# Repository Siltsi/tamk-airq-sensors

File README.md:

# TAMK AIRQ SENSORS  

## TEAM25  

**Members**  
- Eino Lausmaa ([@eino](https://github.com/LausmaaEino))  
- Samu Ojala ([@samu](https://github.com/SamuOj))  
- Tomi Tienhaara ([@tomi](https://github.com/TomiTien))  
- Totti Sillanpää ([@totti](https://github.com/Siltsi))  

## About  

This repository contains a hardware project developed for the **TAMK Summer Training 2025**. The project goal is to design and manifacture a custom circuit board and enclosure for **PCB-based particle sensor systems**.  

All PCBs in this project were designed using **KiCad**.  

## Models  

### ttgo_airq  

The **ttgo_airq** model is based on the LILYGO [T-Display](https://lilygo.cc/products/t-display). This model is currently in a **usable and tested state**.  

**Features:**  
- ESP32 with integrated display  
- Custom-designed PCB  
- 2 enclosure options  

**Enclosures:**  
- **Medium enclosure**  
  - Supports Sensirion [SEN5x](https://sensirion.com/products/catalog/SEK-SEN5x)  
  - Supports Sensirion [SCD41](https://sensirion.com/products/catalog/SEK-SCD41)  
- **Small enclosure**  
  - Supports Sensirion [SCD41](https://sensirion.com/products/catalog/SEK-SCD41) only  

### nodemcu_airq  

The **nodemcu_airq** model is based on the Joy-IT [NodeMCU ESP32](https://joy-it.net/en/products/SBC-NodeMCU-ESP32).  
This model is **still a work in progress**.  

**Current status:**  
- PCB design is expected to be functional  
- System-level development is ongoing  

**Display options:**  
- Large display using the Velleman [VMP400](https://www.velleman.eu/products/view/3-5-320-x-480-touchscreen-for-raspberry-pi-vmp400/?id=438240)  
- Smaller display  
- No display  

**Enclosures:**  
- No enclosures have been designed yet for this model

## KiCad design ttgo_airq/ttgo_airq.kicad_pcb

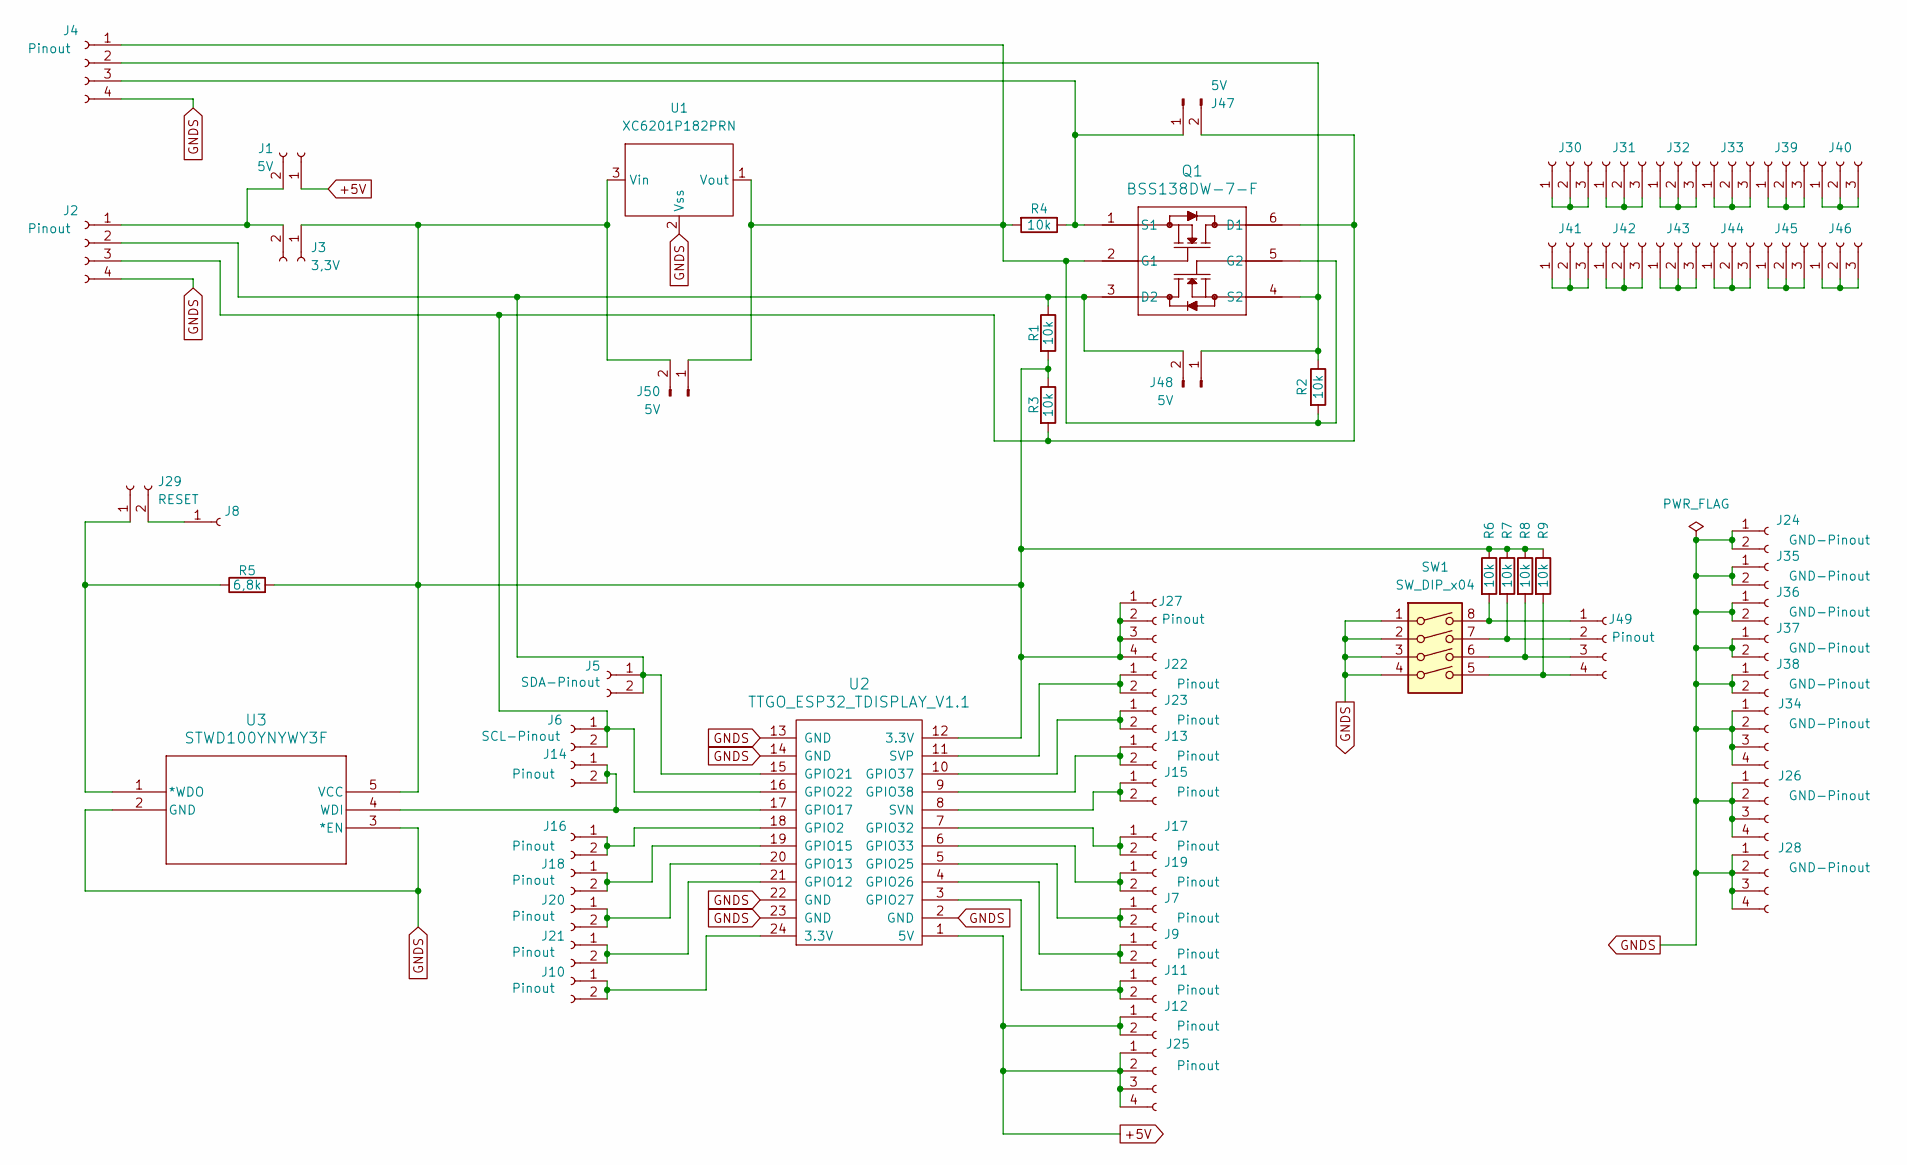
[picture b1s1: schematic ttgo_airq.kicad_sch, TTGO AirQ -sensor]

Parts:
J1: 5V; PinSocket_1x02_P2.54mm_Vertical
J2, J4, J25, J27, J49: Pinout; PinSocket_1x04_P2.54mm_Vertical
J3: 3,3V; PinSocket_1x02_P2.54mm_Vertical
J5: SDA-Pinout; PinSocket_1x02_P2.54mm_Vertical
J6: SCL-Pinout; PinSocket_1x02_P2.54mm_Vertical
J7, J9, J10, J11, J12, J13, J14, J15, J16, J17, J18, J19, J20, J21, J22, J23: Pinout; PinSocket_1x02_P2.54mm_Vertical
J8: PinSocket_1x01_P2.54mm_Vertical
J24, J35, J36, J37, J38: GND-Pinout; PinSocket_1x02_P2.54mm_Vertical
J26, J28, J34: GND-Pinout; PinSocket_1x04_P2.54mm_Vertical
J29: RESET; PinSocket_1x02_P2.54mm_Vertical
J30, J31, J32, J33, J39, J40, J41, J42, J43, J44, J45, J46: Conn_01x03_Socket; PinSocket_1x03_P2.54mm_Vertical
J47, J48, J50: 5V; PinHeader_1x02_P2.54mm_Vertical
Q1: BSS138DW-7-F; SOT363_DIO
R1, R2, R3, R4, R6, R7, R8, R9: 10k; R_1206_3216Metric_Pad1.30x1.75mm_HandSolder
R5: 6,8k; R_1206_3216Metric_Pad1.30x1.75mm_HandSolder
SW1: SW_DIP_x04; SW_DIP_SPSTx04_Piano_10.8x11.72mm_W7.62mm_P2.54mm
U1: XC6201P182PRN
U2: TTGO_ESP32_TDISPLAY_V1.1; TTGO-T-Display
U3: STWD100YNYWY3F; SOT23-5L_STM

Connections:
+5V: J1.1, J12.1, J12.2, J25.1, J25.2, J25.3, J25.4, U2.1 (5V)
GNDS: J2.4, J4.4, J24.1, J24.2, J26.1, J26.2, J26.3, J26.4, J28.1, J28.2, J28.3, J28.4, J34.1, J34.2, J34.3, J34.4, J35.1, J35.2, J36.1, J36.2, J37.1, J37.2, J38.1, J38.2, SW1.1, SW1.2, SW1.3, SW1.4, U1.2 (Vss), U2.2 (GND), U2.13 (GND), U2.14 (GND), U2.22 (GND), U2.23 (GND), U3.2 (GND), U3.3 (*EN)
unnamed: J1.2, J2.1, J3.2
unnamed: J2.2, J5.1, J5.2, J48.2, Q1.3 (D2), R1.1, U2.15 (GPIO21)
unnamed: J2.3, J6.1, J6.2, J47.2, Q1.6 (D1), R3.2, U2.16 (GPIO22)
unnamed: J4.1, J50.1, Q1.2 (G1), Q1.5 (G2), R2.2, R4.2, U1.1 (Vout)
unnamed: J4.2, J48.1, Q1.4 (S2), R2.1
unnamed: J4.3, J47.1, Q1.1 (S1), R4.1
unnamed: J7.1, J7.2, U2.5 (GPIO25)
unnamed: J9.1, J9.2, U2.4 (GPIO26)
unnamed: J10.1, J10.2, U2.24 (3.3V)
unnamed: J11.1, J11.2, U2.3 (GPIO27)
unnamed: J13.1, J13.2, U2.9 (GPIO38)
unnamed: J14.1, J14.2, U2.17 (GPIO17), U3.4 (WDI)
unnamed: J15.1, J15.2, U2.8 (SVN)
unnamed: J16.1, J16.2, U2.18 (GPIO2)
unnamed: J17.1, J17.2, U2.7 (GPIO32)
unnamed: J18.1, J18.2, U2.19 (GPIO15)
unnamed: J19.1, J19.2, U2.6 (GPIO33)
unnamed: J20.1, J20.2, U2.20 (GPIO13)
unnamed: J21.1, J21.2, U2.21 (GPIO12)
unnamed: J22.1, J22.2, U2.11 (SVP)
unnamed: J23.1, J23.2, U2.10 (GPIO37)
unnamed: J3.1, J27.1, J27.2, J27.3, J27.4, J50.2, R1.2, R3.1, R5.2, R6.1, R7.1, R8.1, R9.1, U1.3 (Vin), U2.12 (3.3V), U3.5 (VCC)
unnamed: J29.1, R5.1, U3.1 (*WDO)
unnamed: J8.1, J29.2
unnamed: J30.1, J30.2, J30.3
unnamed: J31.1, J31.2, J31.3
unnamed: J32.1, J32.2, J32.3
unnamed: J33.1, J33.2, J33.3
unnamed: J39.1, J39.2, J39.3
unnamed: J40.1, J40.2, J40.3
unnamed: J41.1, J41.2, J41.3
unnamed: J42.1, J42.2, J42.3
unnamed: J43.1, J43.2, J43.3
unnamed: J44.1, J44.2, J44.3
unnamed: J45.1, J45.2, J45.3
unnamed: J46.1, J46.2, J46.3
unnamed: J49.1, R6.2, SW1.8
unnamed: J49.2, R7.2, SW1.7
unnamed: J49.3, R8.2, SW1.6
unnamed: J49.4, R9.2, SW1.5

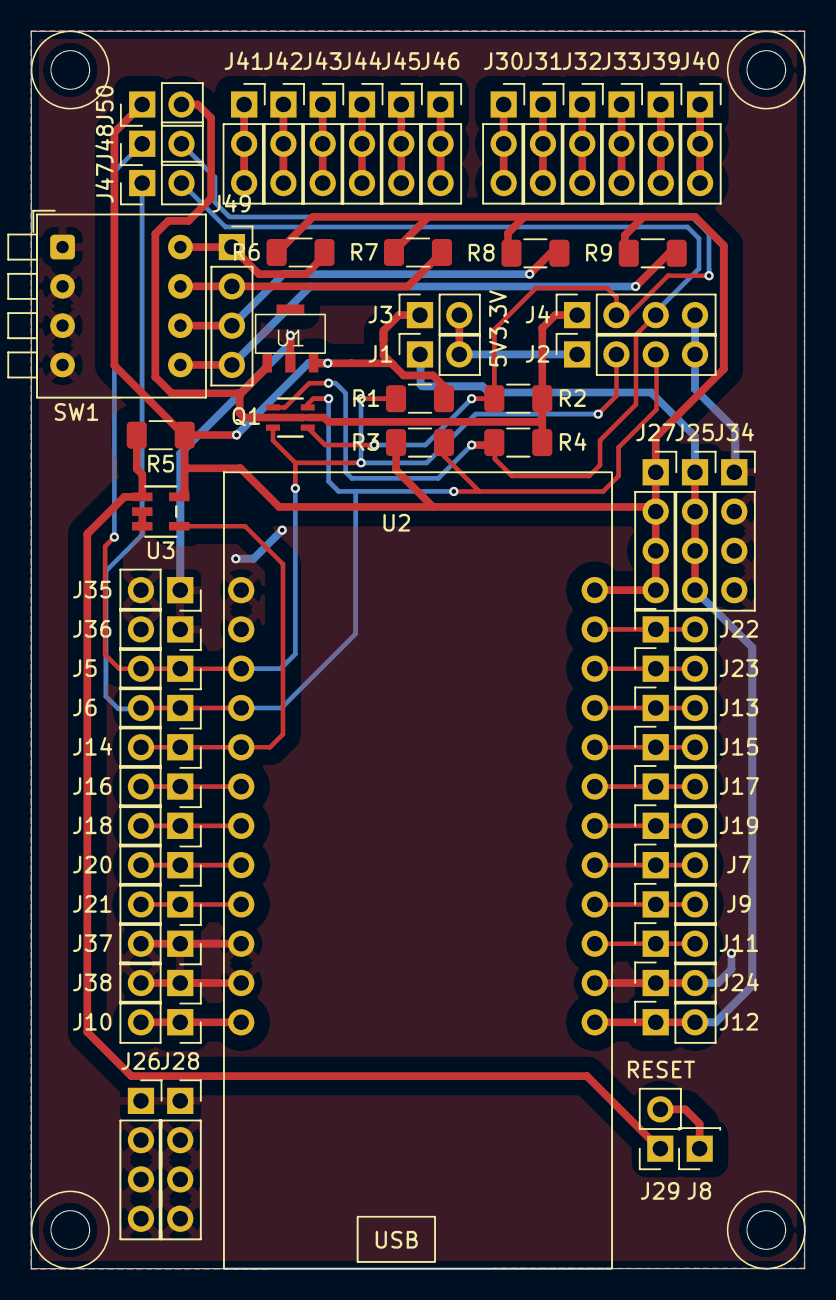
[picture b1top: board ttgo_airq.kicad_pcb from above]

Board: 2 copper layers, 50.0 x 80.0 mm, 64 parts (0 on the bottom side), 42 nets.

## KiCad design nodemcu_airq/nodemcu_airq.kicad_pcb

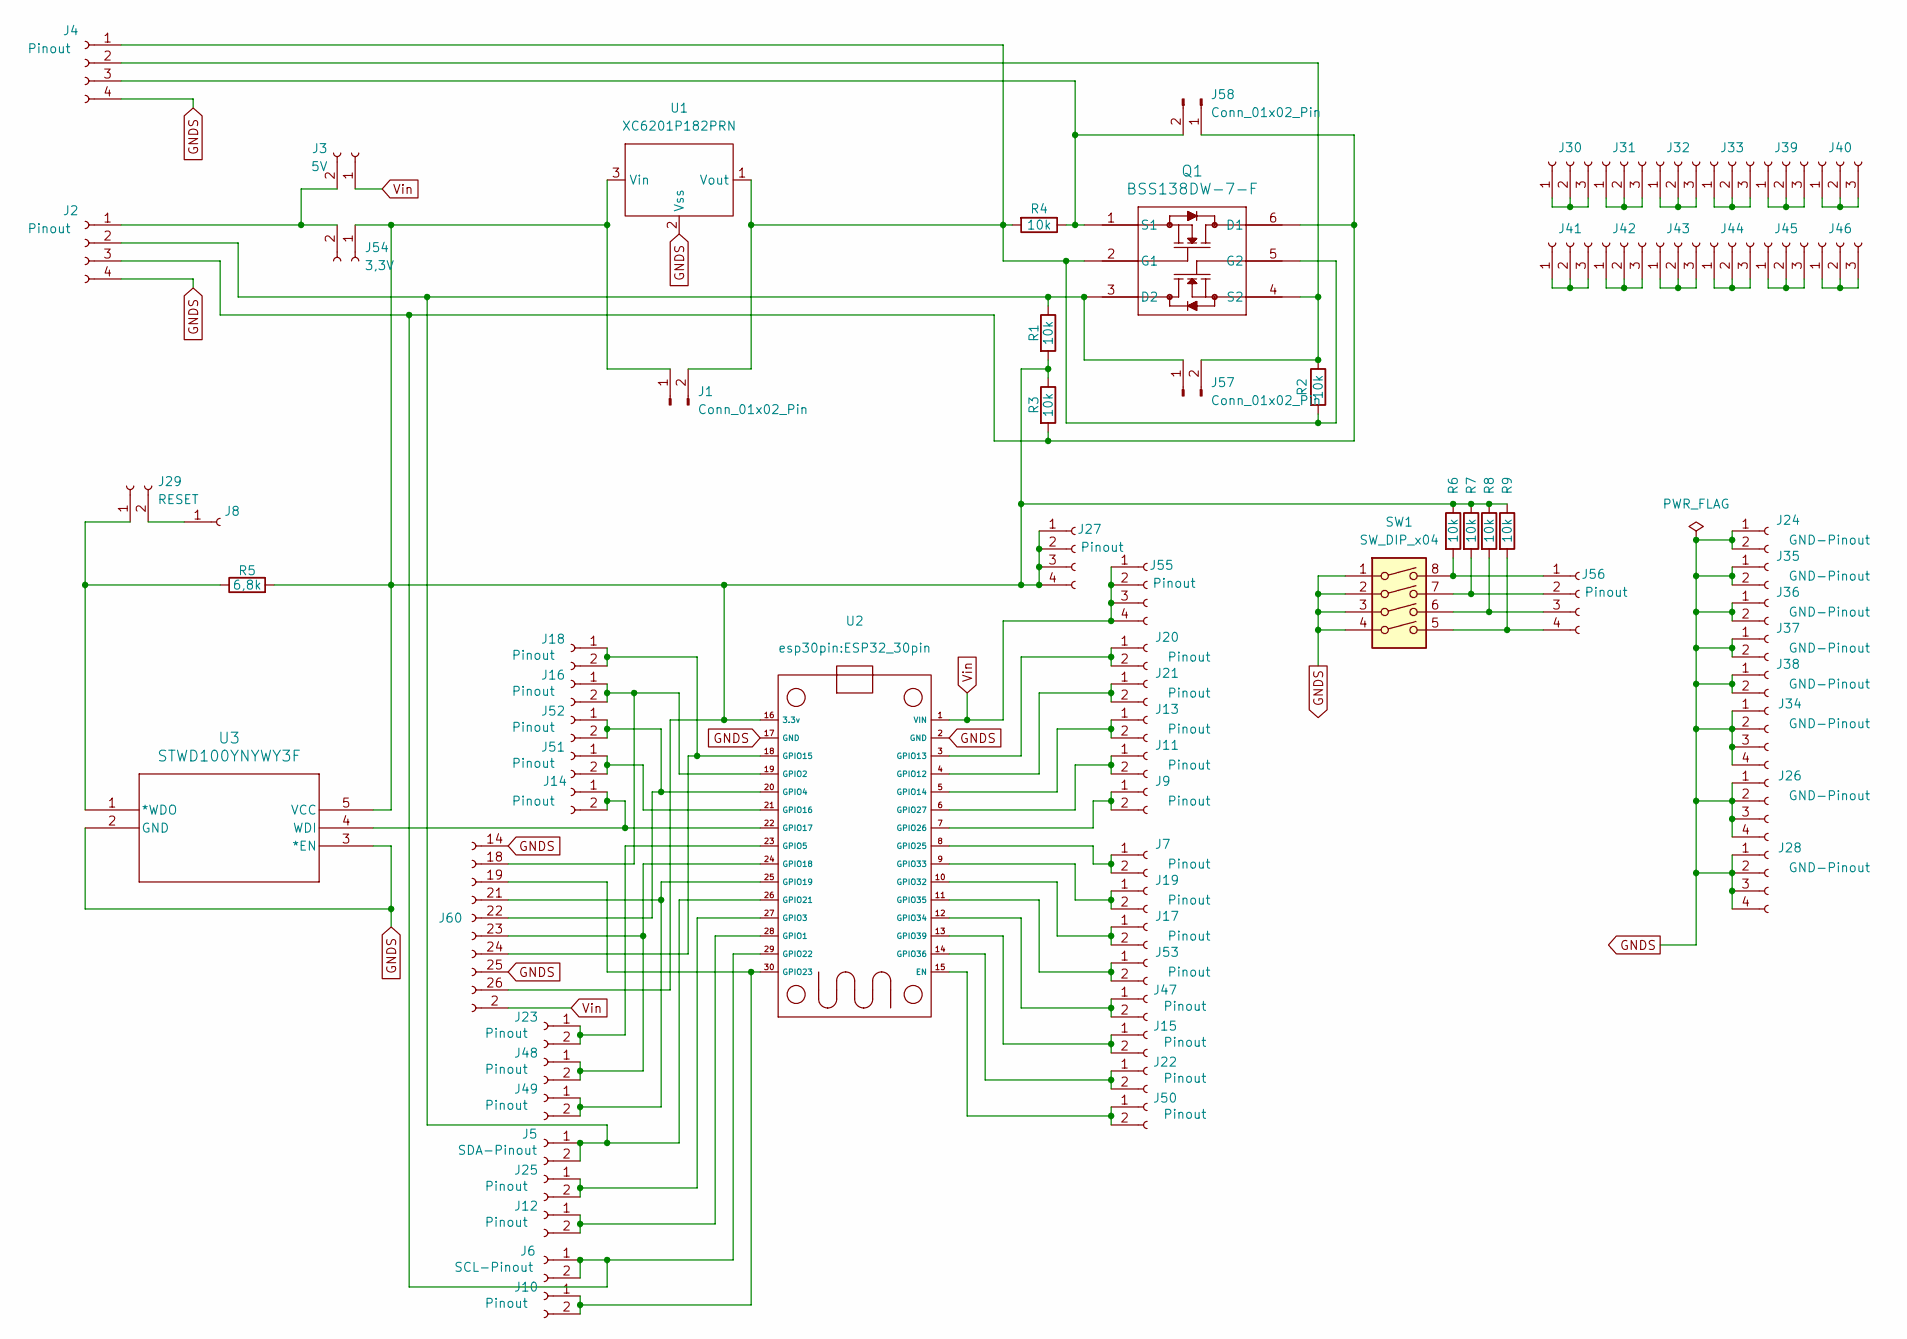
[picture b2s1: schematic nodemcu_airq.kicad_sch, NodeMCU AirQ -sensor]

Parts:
J1, J57, J58: Conn_01x02_Pin; PinHeader_1x02_P2.54mm_Vertical
J2, J4, J27, J55, J56: Pinout; PinSocket_1x04_P2.54mm_Vertical
J3: 5V; PinSocket_1x02_P2.54mm_Vertical
J5: SDA-Pinout; PinSocket_1x02_P2.54mm_Vertical
J6: SCL-Pinout; PinSocket_1x02_P2.54mm_Vertical
J7, J9, J10, J11, J12, J13, J14, J15, J16, J17, J18, J19, J20, J21, J22, J23, J25, J47, J48, J49, J50, J51, J52, J53: Pinout; PinSocket_1x02_P2.54mm_Vertical
J8: PinSocket_1x01_P2.54mm_Vertical
J24, J35, J36, J37, J38: GND-Pinout; PinSocket_1x02_P2.54mm_Vertical
J26, J28, J34: GND-Pinout; PinSocket_1x04_P2.54mm_Vertical
J29: RESET; PinSocket_1x02_P2.54mm_Vertical
J30, J31, J32, J33, J39, J40, J41, J42, J43, J44, J45, J46: Conn_01x03_Socket; PinSocket_1x03_P2.54mm_Vertical
J54: 3,3V; PinSocket_1x02_P2.54mm_Vertical
J60: Conn_01x10_Socket; PinSocket_2x13_P2.54mm_Vertical
Q1: BSS138DW-7-F; SOT363_DIO
R1, R2, R3, R4, R6, R7, R8, R9: 10k; R_1206_3216Metric_Pad1.30x1.75mm_HandSolder
R5: 6,8k; R_1206_3216Metric_Pad1.30x1.75mm_HandSolder
SW1: SW_DIP_x04; SW_DIP_SPSTx04_Piano_10.8x11.72mm_W7.62mm_P2.54mm
U1: XC6201P182PRN
U2: ESP32_30pin
U3: STWD100YNYWY3F; SOT23-5L_STM

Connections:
GNDS: J2.4, J4.4, J24.1, J24.2, J26.1, J26.2, J26.3, J26.4, J28.1, J28.2, J28.3, J28.4, J34.1, J34.2, J34.3, J34.4, J35.1, J35.2, J36.1, J36.2, J37.1, J37.2, J38.1, J38.2, J60.14 (Pin_1), J60.25 (Pin_8), SW1.1, SW1.2, SW1.3, SW1.4, U1.2 (Vss), U2.2 (GND), U2.17 (GND), U3.2 (GND), U3.3 (*EN)
unnamed: J1.1, J27.1, J27.2, J27.3, J27.4, J54.1, J60.26 (Pin_9), R1.2, R3.1, R5.2, R6.1, R7.1, R8.1, R9.1, U1.3 (Vin), U2.16 (3.3v), U3.5 (VCC)
unnamed: J1.2, J4.1, Q1.2 (G1), Q1.5 (G2), R2.2, R4.2, U1.1 (Vout)
unnamed: J2.1, J3.2, J54.2
unnamed: J2.2, J5.1, J5.2, J57.1, Q1.3 (D2), R1.1, U2.26 (GPIO21)
unnamed: J2.3, J6.1, J6.2, J58.1, Q1.6 (D1), R3.2, U2.29 (GPIO22)
unnamed: J4.2, J57.2, Q1.4 (S2), R2.1
unnamed: J4.3, J58.2, Q1.1 (S1), R4.1
unnamed: J7.1, J7.2, U2.8 (GPIO25)
unnamed: J9.1, J9.2, U2.7 (GPIO26)
unnamed: J10.1, J10.2, J60.19 (Pin_3), U2.30 (GPIO23)
unnamed: J11.1, J11.2, U2.6 (GPIO27)
unnamed: J12.1, J12.2, U2.28 (GPIO1)
unnamed: J13.1, J13.2, U2.5 (GPIO14)
unnamed: J14.1, J14.2, U2.22 (GPIO17), U3.4 (WDI)
unnamed: J15.1, J15.2, U2.13 (GPIO39)
unnamed: J16.1, J16.2, J60.18 (Pin_2), U2.19 (GPIO2)
unnamed: J17.1, J17.2, U2.10 (GPIO32)
unnamed: J18.1, J18.2, J60.24 (Pin_7), U2.18 (GPIO15)
unnamed: J19.1, J19.2, U2.9 (GPIO33)
unnamed: J20.1, J20.2, U2.3 (GPIO13)
unnamed: J21.1, J21.2, U2.4 (GPIO12)
unnamed: J22.1, J22.2, U2.14 (GPIO36)
unnamed: J23.1, J23.2, U2.23 (GPIO5)
unnamed: J25.1, J25.2, U2.27 (GPIO3)
unnamed: J29.1, R5.1, U3.1 (*WDO)
unnamed: J8.1, J29.2
unnamed: J30.1, J30.2, J30.3
unnamed: J31.1, J31.2, J31.3
unnamed: J32.1, J32.2, J32.3
unnamed: J33.1, J33.2, J33.3
unnamed: J39.1, J39.2, J39.3
unnamed: J40.1, J40.2, J40.3
unnamed: J41.1, J41.2, J41.3
unnamed: J42.1, J42.2, J42.3
unnamed: J43.1, J43.2, J43.3
unnamed: J44.1, J44.2, J44.3
unnamed: J45.1, J45.2, J45.3
unnamed: J46.1, J46.2, J46.3
unnamed: J47.1, J47.2, U2.12 (GPIO34)
unnamed: J48.1, J48.2, J60.23 (Pin_6), U2.24 (GPIO18)
unnamed: J49.1, J49.2, J60.21 (Pin_4), U2.25 (GPIO19)
unnamed: J50.1, J50.2, U2.15 (EN)
unnamed: J51.1, J51.2, U2.21 (GPIO16)
unnamed: J52.1, J52.2, J60.22 (Pin_5), U2.20 (GPIO4)
unnamed: J53.1, J53.2, U2.11 (GPIO35)
unnamed: J56.1, R6.2, SW1.8
unnamed: J56.2, R7.2, SW1.7
unnamed: J56.3, R8.2, SW1.6
unnamed: J56.4, R9.2, SW1.5
Vin: J3.1, J55.1, J55.2, J55.3, J55.4, J60.2 (Pin_10), U2.1 (VIN)

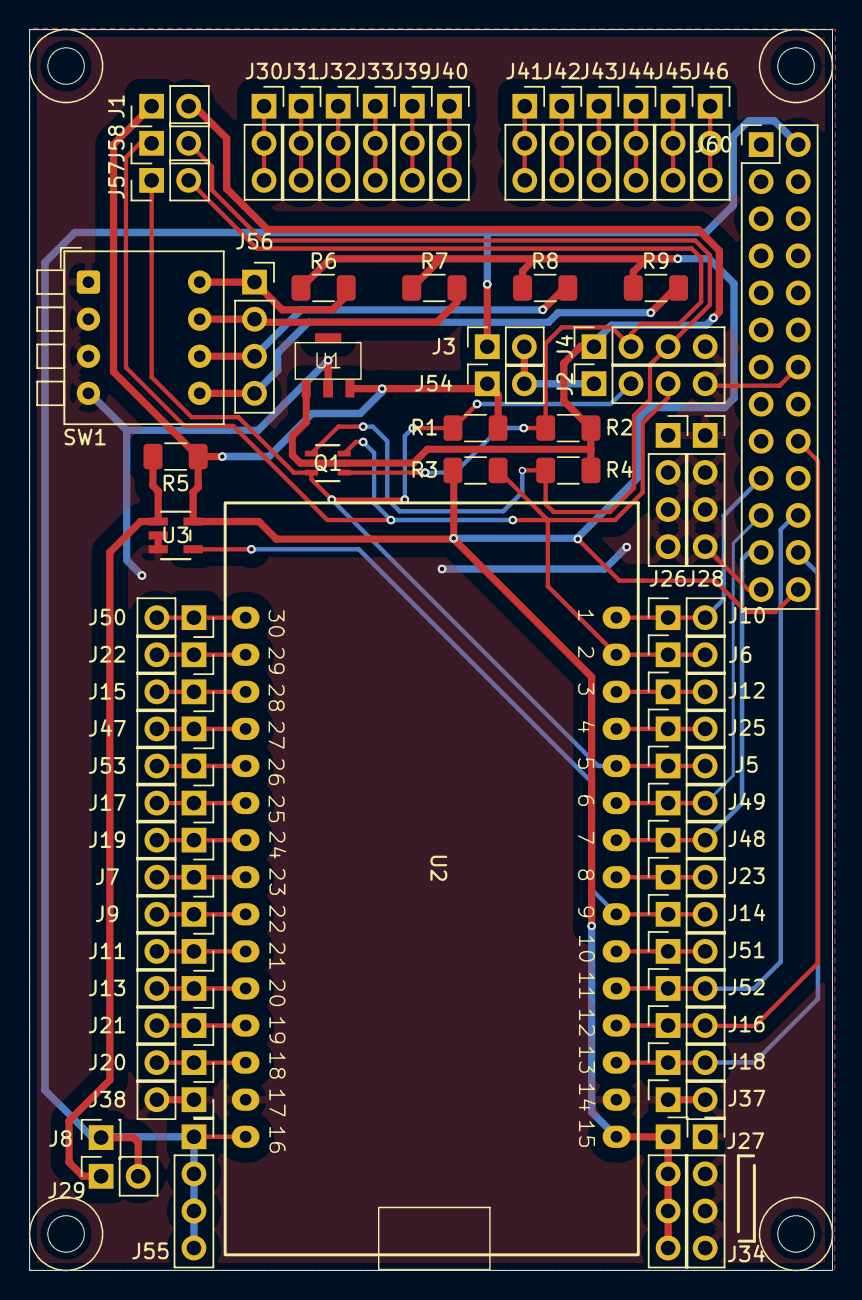
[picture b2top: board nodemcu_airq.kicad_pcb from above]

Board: 2 copper layers, 55.0 x 85.0 mm, 70 parts (0 on the bottom side), 51 nets.

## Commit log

2026-02-03 Added TTGO and NodeMCU -projects
2026-02-04 Added TTGO cases
2026-02-04 Added Schematic and PCB pdfs
2026-02-04 Moved .gitignore
2026-02-05 Added README
